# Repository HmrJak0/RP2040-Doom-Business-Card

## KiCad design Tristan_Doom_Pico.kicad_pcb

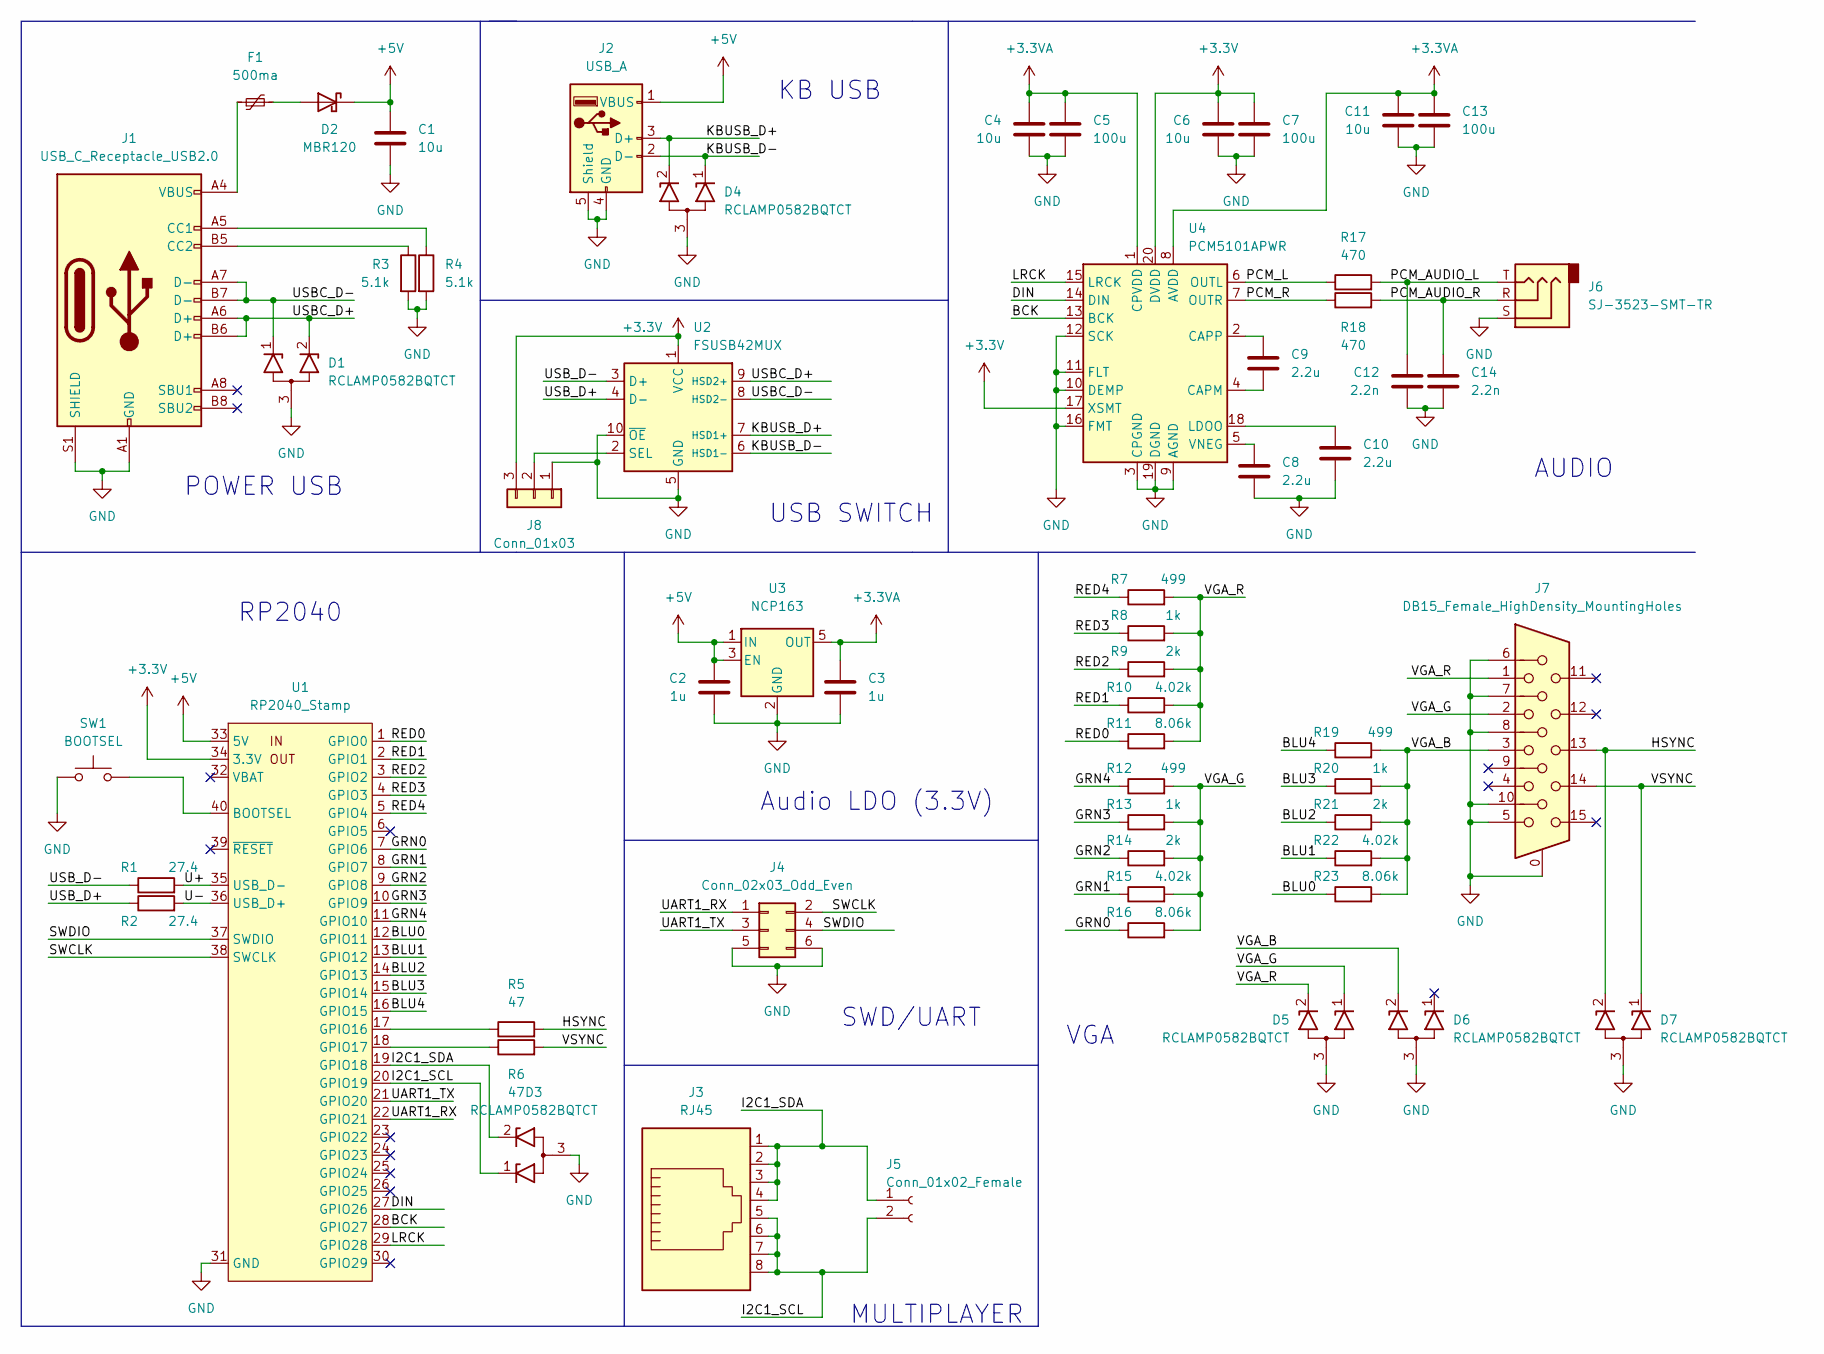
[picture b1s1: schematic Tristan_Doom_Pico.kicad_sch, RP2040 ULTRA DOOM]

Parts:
C1, C4, C6, C11: 10u; C_0805_2012Metric
C2, C3: 1u; C_0805_2012Metric
C5, C7, C13: 100u; C_1210_3225Metric
C8, C9, C10: 2.2u; C_0603_1608Metric
C12, C14: 2.2n; C_0603_1608Metric
D1, D3, D4, D5, D6, D7: RCLAMP0582BQTCT; TVS_RCLAMP0502B.TCT; MouserPN 947-RCLAMP0582BQTCT
D2: MBR120; D_SOD-123F
F1: 500ma; Fuse_1206_3216Metric
J1: USB_C_Receptacle_USB2.0; USB_C_Receptacle_JAE_DX07S016JA1R1500; MouserPN 656-DX07S016JA1R1500
J2: USB_A; USB_A_Stewart_SS-52100-001_Horizontal; MouserPN 530-SS-52100-001
J3: RJ45; RJ45_Amphenol_54602-x08_Horizontal; MouserPN 649-54602-908LF
J4: Conn_02x03_Odd_Even; PinHeader_2x03_P2.54mm_Vertical
J5: Conn_01x02_Female; PinHeader_1x02_P2.54mm_Vertical
J6: SJ-3523-SMT-TR; SJ3523SMTTR; Mouser Part Number 490-SJ-3523-SMT-TR
J7: DB15_Female_HighDensity_MountingHoles; L77HDE15SD1CH4RHNVGA
J8: Conn_01x03; PinHeader_1x03_P2.54mm_Vertical
R1, R2: 27.4; R_1206_3216Metric; MouserPN 71-CRCW120627R4FKTB
R3, R4: 5.1k; R_1206_3216Metric; MouserPN 71-CRCW12065K10FKEAC
R5, R6: 47; R_1206_3216Metric; MouserPN 71-CRCW120647R0FKEAC
R7, R12, R19: 499; R_1206_3216Metric; MouserPN 71-CRCW1206499RFKEAC
R8, R13, R20: 1k; R_1206_3216Metric; MouserPN 71-CRCW12061K00FKEAC
R9, R14, R21: 2k; R_1206_3216Metric; MouserPN 71-CRCW12062K00FKEAC
R10, R15, R22: 4.02k; R_1206_3216Metric; MouserPN 71-CRCW12064K02FKEAC
R11, R16, R23: 8.06k; R_1206_3216Metric; MouserPN 71-CRCW1206-8.66K-E3
R17, R18: 470; R_1206_3216Metric; MouserPN 71-CRCW1206470RFKEAC
SW1: BOOTSEL; SW_PUSH_6mm
U1: RP2040_Stamp; RP2040_Stamp_THT
U2: FSUSB42MUX; MSOP-10_3x3mm_P0.5mm; MouserPN 512-FSUSB42MUX
U3: NCP163; SOT-23-5
U4: PCM5101APWR; TSSOP-20_4.4x6.5mm_P0.65mm

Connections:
+3.3VA: C3.1, C4.1, C5.1, C11.1, C13.1, U3.5 (OUT), U4.1 (CPVDD), U4.8 (AVDD)
+3V3: C6.1, C7.1, J8.3, U1.34 (3.3V), U2.1 (VCC), U4.17 (XSMT), U4.20 (DVDD)
+5V: C1.1, C2.1, D2.1 (K), J2.1 (VBUS), U1.33 (5V), U3.1 (IN), U3.3 (EN)
/BCK: U1.28 (GPIO27), U4.13 (BCK)
/BLU0: R23.1, U1.12 (GPIO11)
/BLU1: R22.1, U1.13 (GPIO12)
/BLU2: R21.1, U1.14 (GPIO13)
/BLU3: R20.1, U1.15 (GPIO14)
/BLU4: R19.1, U1.16 (GPIO15)
/DIN: U1.27 (GPIO26), U4.14 (DIN)
/GRN0: R16.1, U1.7 (GPIO6)
/GRN1: R15.1, U1.8 (GPIO7)
/GRN2: R14.1, U1.9 (GPIO8)
/GRN3: R13.1, U1.10 (GPIO9)
/GRN4: R12.1, U1.11 (GPIO10)
/HSYNC: D7.2 (K2), J7.13, R5.2
/I2C1_SCL: D3.1 (K1), J3.5, J3.6, J3.7, J3.8, J5.2, U1.20 (GPIO19)
/I2C1_SDA: D3.2 (K2), J3.1, J3.2, J3.3, J3.4, J5.1, U1.19 (GPIO18)
/KBUSB_D+: D4.2 (K2), J2.3 (D+), U2.7 (HSD1+)
/KBUSB_D-: D4.1 (K1), J2.2 (D-), U2.6 (HSD1-)
/LRCK: U1.29 (GPIO28), U4.15 (LRCK)
/PCM_AUDIO_L: C12.1, J6.T, R17.2
/PCM_AUDIO_R: C14.1, J6.R, R18.2
/PCM_L: R17.1, U4.6 (OUTL)
/PCM_R: R18.1, U4.7 (OUTR)
/RED0: R11.1, U1.1 (GPIO0)
/RED1: R10.1, U1.2 (GPIO1)
/RED2: R9.1, U1.3 (GPIO2)
/RED3: R8.1, U1.4 (GPIO3)
/RED4: R7.1, U1.5 (GPIO4)
/SWCLK: J4.2, U1.38 (SWCLK)
/SWDIO: J4.4, U1.37 (SWDIO)
/U+: R1.2, U1.35 (USB_D-)
/U-: R2.2, U1.36 (USB_D+)
/UART1_RX: J4.1, U1.22 (GPIO21)
/UART1_TX: J4.3, U1.21 (GPIO20)
/USBC_D+: D1.2 (K2), J1.A6 (D+), J1.B6 (D+), U2.9 (HSD2+)
/USBC_D-: D1.1 (K1), J1.A7 (D-), J1.B7 (D-), U2.8 (HSD2-)
/USB_D+: R2.1, U2.4 (D-)
/USB_D-: R1.1, U2.3 (D+)
/VGA_B: D6.2 (K2), J7.3, R19.2, R20.2, R21.2, R22.2, R23.2
/VGA_G: D5.1 (K1), J7.2, R12.2, R13.2, R14.2, R15.2, R16.2
/VGA_R: D5.2 (K2), J7.1, R7.2, R8.2, R9.2, R10.2, R11.2
/VSYNC: D7.1 (K1), J7.14, R6.2
GND: C1.2, C2.2, C3.2, C4.2, C5.2, C6.2, C7.2, C8.2, C10.2, C11.2, C12.2, C13.2, C14.2, D1.3 (A), D3.3 (A), D4.3 (A), D5.3 (A), D6.3 (A), D7.3 (A), J1.A1 (GND), J1.A12 (GND), J1.B1 (GND), J1.B12 (GND), J1.S1 (SHIELD), J2.4 (GND), J2.5 (Shield), J4.5, J4.6, J6.S, J7.0, J7.5, J7.6, J7.7, J7.8, J7.10, J8.1, R3.2, R4.2, SW1.1, U1.31 (GND), U2.5 (GND), U2.10 (~OE), U3.2 (GND), U4.3 (CPGND), U4.9 (AGND), U4.10 (DEMP), U4.11 (FLT), U4.12 (SCK), U4.16 (FMT), U4.19 (DGND)
unnamed: C8.1, U4.5 (VNEG)
unnamed: C9.1, U4.2 (CAPP)
unnamed: C9.2, U4.4 (CAPM)
unnamed: C10.1, U4.18 (LDOO)
unnamed: D2.2 (A), F1.2
unnamed: F1.1, J1.A4 (VBUS), J1.A9 (VBUS), J1.B4 (VBUS), J1.B9 (VBUS)
unnamed: J1.A5 (CC1), R4.1
unnamed: J1.B5 (CC2), R3.1
unnamed: J8.2, U2.2 (SEL)
unnamed: R5.1, U1.17 (GPIO16)
unnamed: R6.1, U1.18 (GPIO17)
unnamed: SW1.2, U1.40 (BOOTSEL)

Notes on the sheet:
VGA
Audio LDO (3.3V)
SWD/UART
MULTIPLAYER
USB SWITCH
POWER USB
AUDIO
RP2040
KB USB

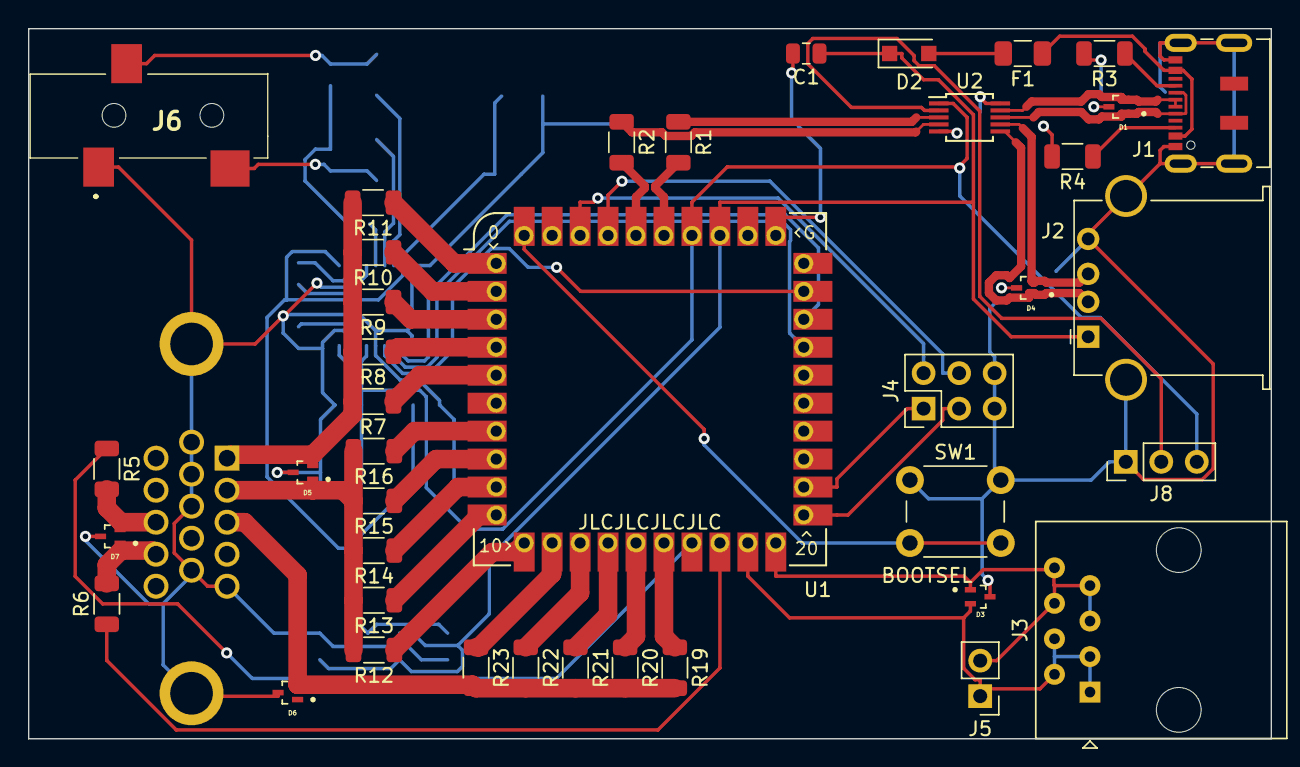
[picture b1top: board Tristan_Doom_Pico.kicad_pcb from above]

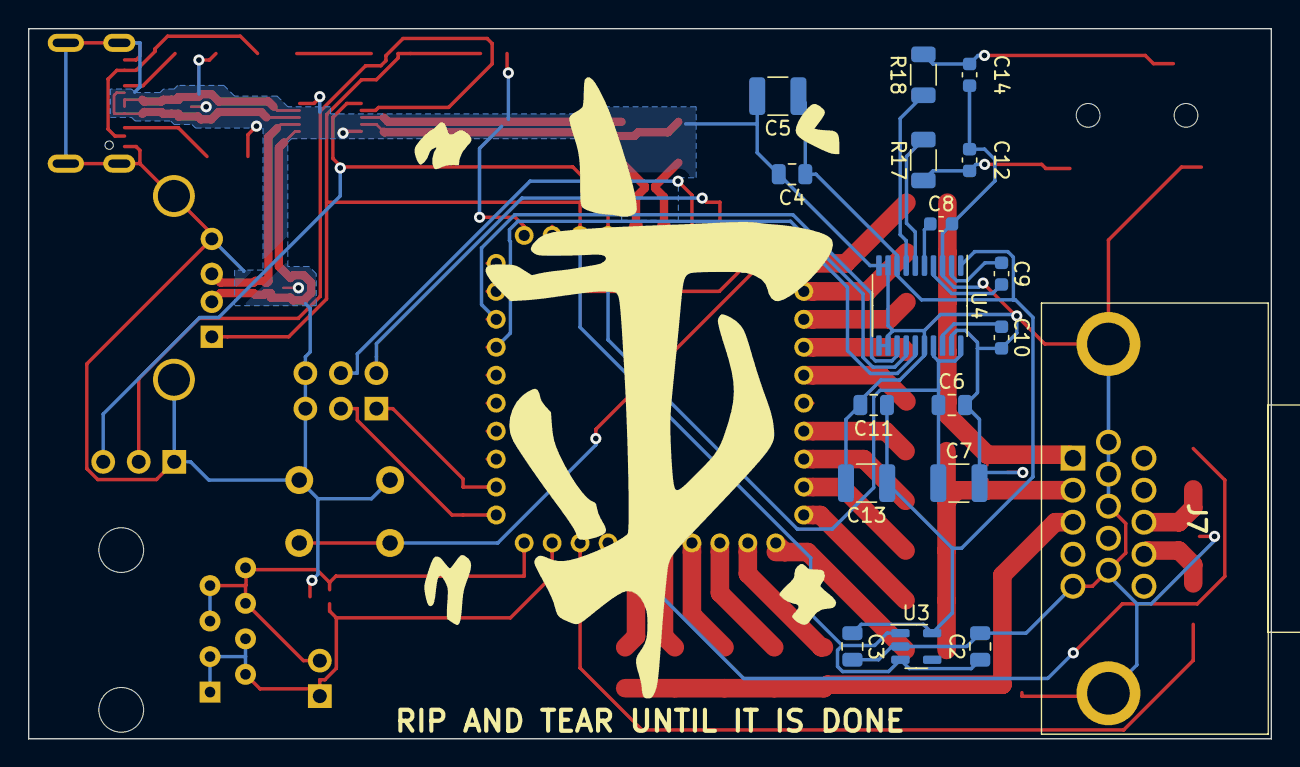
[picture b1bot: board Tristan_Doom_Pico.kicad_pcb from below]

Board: 2 copper layers, 88.9 x 50.8 mm, 58 parts (18 on the bottom side), 57 nets.

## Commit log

2022-09-13 v1.0 - First Boards sent to JLCPCB

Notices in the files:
Tristan_Doom_Pico.kicad_sch:
Creative Commons BY-NC-SA 4.0
